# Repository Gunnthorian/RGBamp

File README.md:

<!--
Title: RGB amplifier
Description: RGB amplifier used with Arduino or Raspberry Pi to control 12v LED light strips.
Author: Gunnar Bjorkman
-->

<h3>RGBamp</h3>

This project ties in nicely with https://github.com/Gunnthorian/homebridge-pwmhat my homebridge smart home program

<h4>This is an open source hardware project -- RGB amplifier 0-5v to 0-12v</h4>

Designed by Gunnar Bjorkman

<h4>About</h4>
This is a small project that I wanted to work on, I use a perma-proto board from this design currently to control my RGB light strip on my desk. Here is an opensource schematic of the board for anyone to use and manufacture themselves (I used PCBway.com, it was a total of $18 to get 10 of the bare boards made and shipped to my house)

<h4>Purpose</h4>
This RGB amplifier is great for Arduino projects and can be used with Raspberry Pi projects, for a Pi you just need to use a pwm hat to output the 5v signal needed to get the brightest lights (this is what I do).

<h4>Usage</h4>
The board takes 3 signal wires in (RGB 0v-5v), 1 GND from the source of the signal wires, and 12v power supply. The outputs are +12v and RGB -12v (proportinal to the RGB signal wires).

<div style="height:500px">

</div>
<br>
<div style="width:500px">
  BOM:
  <li>3 -- 330Ω resistors</li>
  <li>1 -- 16v 220µf capacitor</li>
  <li>1 -- 12v power jack <a href="https://www.sparkfun.com/products/119">link to part on Sparkfun's site</a></li>
  <li>2 -- 4 pin headers (preferably 90°)</li>
  <li>3 -- TIP31C mosfet transistors</li>
  </div>

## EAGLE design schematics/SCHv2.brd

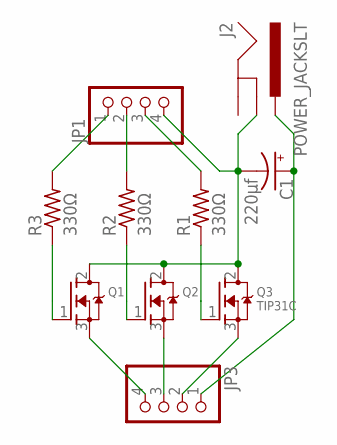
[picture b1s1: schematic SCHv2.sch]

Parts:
C1: 220µf; E2,5-7
J2: POWER_JACKSLT; POWER_JACK_SLOT
JP1, JP3: PINHD-1X4/90; 1X04/90
Q1, Q2: MOSFET-NGDS_TO220V; TO220V
Q3: TIP31C; TO220V
R1, R2, R3: 330Ω; 0207/7

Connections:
unnamed: JP1.1, R3.2
unnamed: JP1.2, R2.2
unnamed: JP1.3, R1.2
unnamed: C1.-, J2.GND@1 (GNDBREAK), JP1.4, Q1.2 (D), Q2.2 (D), Q3.2 (D)
unnamed: C1.+, J2.PWR, JP3.1
unnamed: Q1.1 (G), R3.1
unnamed: Q2.1 (G), R2.1
unnamed: Q3.1 (G), R1.1
unnamed: JP3.2, Q3.3 (S)
unnamed: JP3.3, Q2.3 (S)
unnamed: JP3.4, Q1.3 (S)

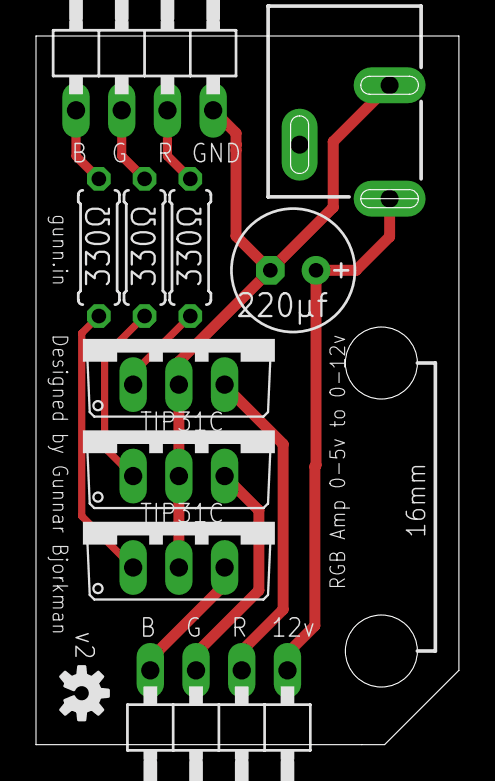
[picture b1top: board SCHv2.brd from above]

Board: 2 copper layers, 23.5 x 39.4 mm, 11 parts (0 on the bottom side), 11 nets.

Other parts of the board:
U$2: OSHW-LOGO-S

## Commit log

2018-10-08 uploading the schematics for the board
2018-10-08 rendering of my project
2018-10-08 schematic upload
2018-10-08 uploading new images
2018-10-08 list styling didnt come out as planned
2018-10-08 can't use md and html styling in same md
2018-10-08 display: inline
2018-10-08 making things look nice
2018-10-08 making them inline
2018-10-08 my last fix didnt do anything for obvious reasons
2018-10-09 updating the readme
2018-10-12 fixing wiring (power jack)
    turns out the ground of the power jack was swapped with the signal pin on the jack, all fixed in this push. sadly I have 10 boards with this issue, easy fix though. 👍

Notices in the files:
parts and their libraries:
SparkFun-Aesthetics: Licensing: Creative Commons ShareAlike 4.0 International - https://creativecommons.org/licenses/by-sa/4.0
